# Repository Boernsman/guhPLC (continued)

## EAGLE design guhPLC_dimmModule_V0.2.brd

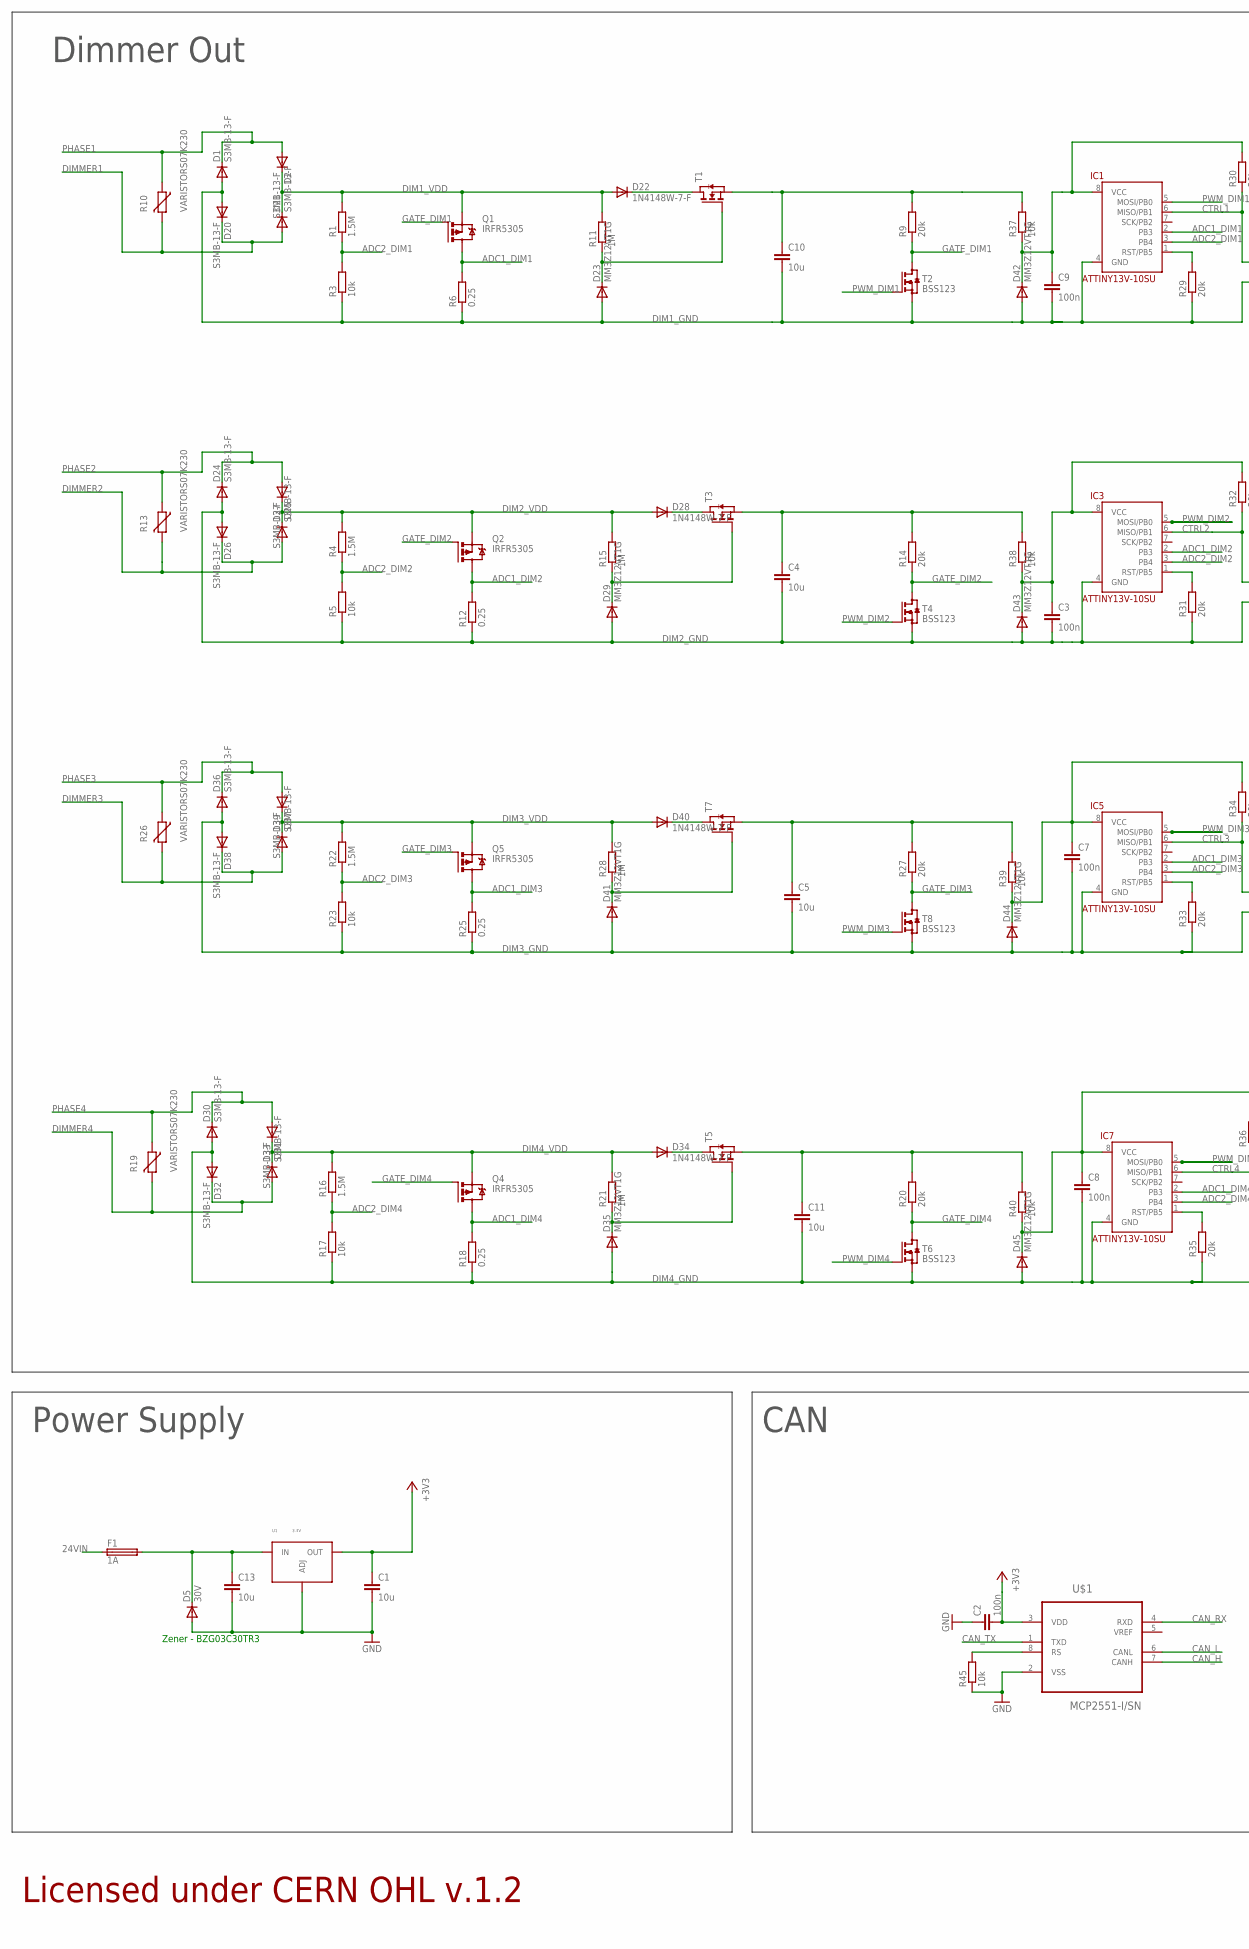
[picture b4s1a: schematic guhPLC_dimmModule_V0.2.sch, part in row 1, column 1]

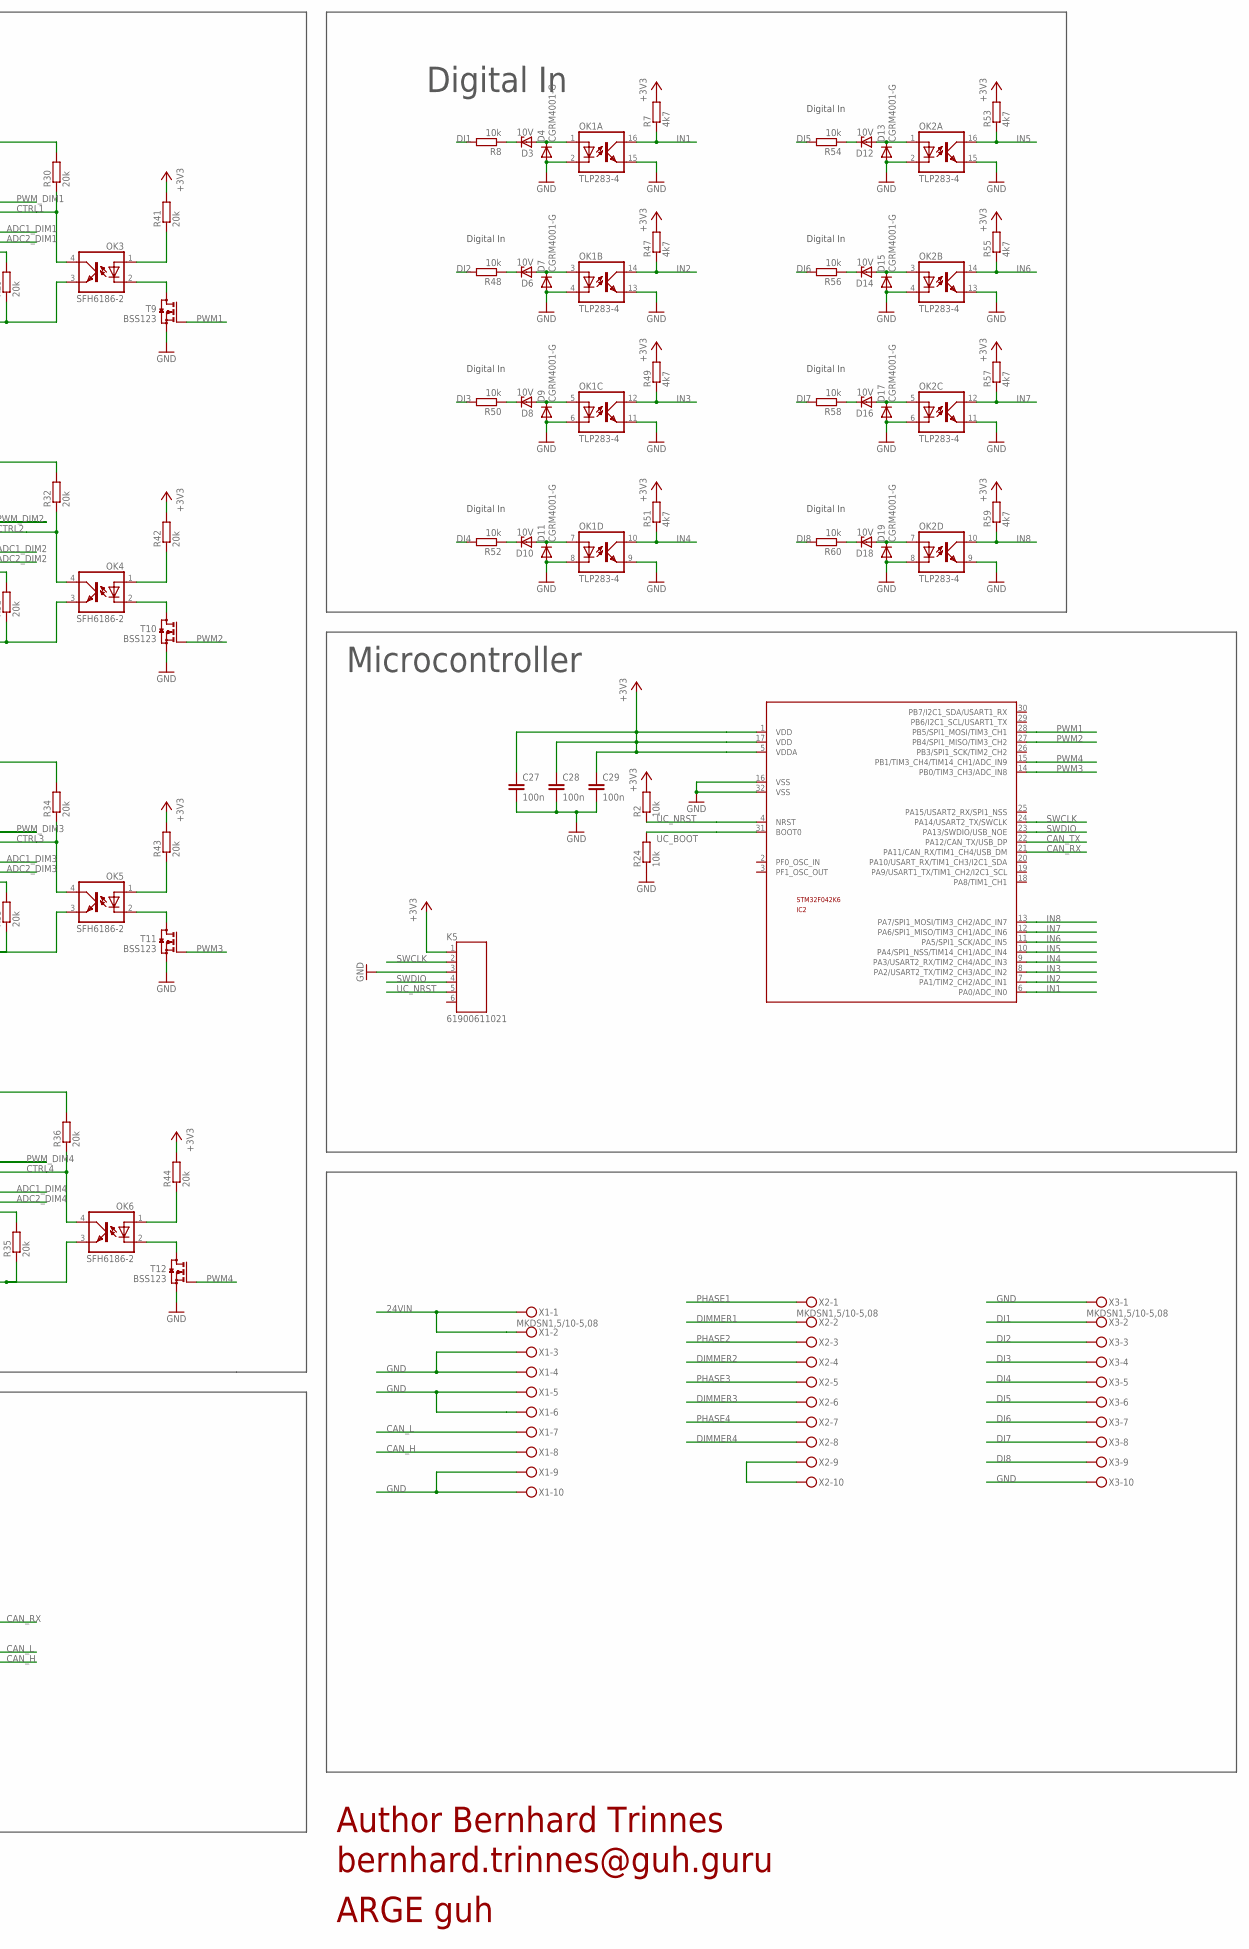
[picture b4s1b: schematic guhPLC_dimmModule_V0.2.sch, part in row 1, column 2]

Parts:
C1, C4, C5, C10, C11, C13: 10u; C1206
C2, C3, C7, C8, C9, C27, C28, C29: 100n; C0603
D1, D2, D20, D21, D24, D25, D26, D27, D30, D31, D32, D33, D36, D37, D38, D39: S3MB-13-F; DO214AA
D3, D6, D8, D10, D12, D14, D16, D18: 10V; SOD80C
D4, D7, D9, D11, D13, D15, D17, D19: CGRM4001-G; SOD-123_MINI-SMA
D5: 30V; DO214AC
D22, D28, D34, D40: 1N4148W-7-F; SOD123
D23, D29, D35, D41, D42, D43, D44, D45: MM3Z12VT1G; SOD323-W
F1: 1A; LITTLEFUSE
IC1, IC3, IC5, IC7: ATTINY13V-10SU; SOIC8
IC2: STM32F042K6; LQFP32-7X7
K5: 61900611021
OK1, OK2: TLP283-4; MINI-FLAT-16
OK3, OK4, OK5, OK6: SFH6186-2; SMD4
Q1, Q2, Q4, Q5: IRFR5305; D-PAK_TO252AA
R1: 1.5M; R1206
R2, R24, R45: 10k; R0603
R3: 10k; R1206
R4, R16, R22: 1.5M; M1206
R5, R17, R23, R37, R38, R39, R40: 10k; M1206
R6: 0.25; R1206
R7, R47, R49, R51, R53, R55, R57, R59: 4k7; R0603
R8, R48, R50, R52, R54, R56, R58, R60: 10k; R0805
R9, R14, R20, R27: 20k; M1206
R10, R13, R19, R26: VARISTORS07K230; S07K230
R11: 1M; R1206
R12, R18, R25: 0.25; M1206
R15, R21, R28: 1M; M1206
R29, R30, R31, R32, R33, R34, R35, R36, R41, R42, R43, R44: 20k; R0603
T1, T3, T5, T7: NMOSSOT23; SOT-23
T2, T4, T6, T8, T9, T10, T11, T12: BSS123; SOT23
U1: 3.3V; TO-252-3L
U$1: MCP2551-I/SN; SOIC127P600X175-8N
X1, X2, X3: MKDSN1,5/10-5,08

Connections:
24VIN: F1.1, X1.1, X1.2
+3V3: C1.1, C2.2, C27.1, C28.1, C29.1, IC2.1 (VDD), IC2.5 (VDDA), IC2.17 (VDD), K5.1, R2.2, R7.2, R41.2, R42.2, R43.2, R44.2, R47.2, R49.2, R51.2, R53.2, R55.2, R57.2, R59.2, U1.PAD (OUT), U$1.3 (VDD)
ADC1_DIM1: IC1.2 (PB3), Q1.4 (D), R6.2
ADC1_DIM2: IC3.2 (PB3), Q2.4 (D), R12.2
ADC1_DIM3: IC5.2 (PB3), Q5.4 (D), R25.2
ADC1_DIM4: IC7.2 (PB3), Q4.4 (D), R18.2
ADC2_DIM1: IC1.3 (PB4), R1.1, R3.2
ADC2_DIM2: IC3.3 (PB4), R4.1, R5.2
ADC2_DIM3: IC5.3 (PB4), R22.1, R23.2
ADC2_DIM4: IC7.3 (PB4), R16.1, R17.2
CAN_H: U$1.7 (CANH), X1.8
CAN_L: U$1.6 (CANL), X1.7
CAN_RX: IC2.21 (PA11/CAN_RX/TIM1_CH4/USB_DM), U$1.4 (RXD)
CAN_TX: IC2.22 (PA12/CAN_TX/USB_DP), U$1.1 (TXD)
CTRL1: IC1.6 (MISO/PB1), OK3.4 (COL), R30.1
CTRL2: IC3.6 (MISO/PB1), OK4.4 (COL), R32.1
CTRL3: IC5.6 (MISO/PB1), OK5.4 (COL), R34.1
CTRL4: IC7.6 (MISO/PB1), OK6.4 (COL), R36.1
DI1: R8.2, X3.2
DI2: R48.2, X3.3
DI3: R50.2, X3.4
DI4: R52.2, X3.5
DI5: R54.2, X3.6
DI6: R56.2, X3.7
DI7: R58.2, X3.8
DI8: R60.2, X3.9
DIM1_GND: C9.2, C10.2, D1.A, D20.A, D23.A, D42.A, IC1.4 (GND), OK3.3 (EMIT), R3.1, R6.1, R29.1, T2.2 (S)
DIM1_VDD: D2.C, D21.C, D22.A, Q1.3 (S), R1.2, R11.2
DIM2_GND: C3.2, C4.2, D24.A, D26.A, D29.A, D43.A, IC3.4 (GND), OK4.3 (EMIT), R5.1, R12.1, R31.1, T4.2 (S)
DIM2_VDD: D25.C, D27.C, D28.A, Q2.3 (S), R4.2, R15.2
DIM3_GND: C5.2, C7.2, D36.A, D38.A, D41.A, D44.A, IC5.4 (GND), OK5.3 (EMIT), R23.1, R25.1, R33.1, T8.2 (S)
DIM3_VDD: D37.C, D39.C, D40.A, Q5.3 (S), R22.2, R28.2
DIM4_GND: C8.2, C11.2, D30.A, D32.A, D35.A, D45.A, IC7.4 (GND), OK6.3 (EMIT), R17.1, R18.1, R35.1, T6.2 (S)
DIM4_VDD: D31.C, D33.C, D34.A, Q4.3 (S), R16.2, R21.2
DIMMER1: D20.C, D21.A, R10.2, X2.2
DIMMER2: D26.C, D27.A, R13.2, X2.4
DIMMER3: D38.C, D39.A, R26.2, X2.6
DIMMER4: D32.C, D33.A, R19.2, X2.8
GATE_DIM1: Q1.1 (G), R9.1, T2.3 (D)
GATE_DIM2: Q2.1 (G), R14.1, T4.3 (D)
GATE_DIM3: Q5.1 (G), R27.1, T8.3 (D)
GATE_DIM4: Q4.1 (G), R20.1, T6.3 (D)
GND: C1.2, C2.1, C13.2, C27.2, C28.2, C29.2, D4.A, D5.A, D7.A, D9.A, D11.A, D13.A, D15.A, D17.A, D19.A, IC2.16 (VSS), IC2.32 (VSS), K5.3, OK1.2 (C), OK1.4 (C), OK1.6 (C), OK1.8 (C), OK1.9 (EMIT), OK1.11 (EMIT), OK1.13 (EMIT), OK1.15 (EMIT), OK2.2 (C), OK2.4 (C), OK2.6 (C), OK2.8 (C), OK2.9 (EMIT), OK2.11 (EMIT), OK2.13 (EMIT), OK2.15 (EMIT), R24.1, R45.1, T9.2 (S), T10.2 (S), T11.2 (S), T12.2 (S), U1.1 (ADJ), U$1.2 (VSS), X1.3, X1.4, X1.5, X1.6, X1.9, X1.10, X3.1, X3.10
IN1: IC2.6 (PA0/ADC_IN0), OK1.16 (COL), R7.1
IN2: IC2.7 (PA1/TIM2_CH2/ADC_IN1), OK1.14 (COL), R47.1
IN3: IC2.8 (PA2/USART2_TX/TIM2_CH3/ADC_IN2), OK1.12 (COL), R49.1
IN4: IC2.9 (PA3/USART2_RX/TIM2_CH4/ADC_IN3), OK1.10 (COL), R51.1
IN5: IC2.10 (PA4/SPI1_NSS/TIM14_CH1/ADC_IN4), OK2.16 (COL), R53.1
IN6: IC2.11 (PA5/SPI1_SCK/ADC_IN5), OK2.14 (COL), R55.1
IN7: IC2.12 (PA6/SPI1_MISO/TIM3_CH1/ADC_IN6), OK2.12 (COL), R57.1
IN8: IC2.13 (PA7/SPI1_MOSI/TIM3_CH2/ADC_IN7), OK2.10 (COL), R59.1
unnamed: C8.1, D45.C, IC7.8 (VCC), R36.2, R40.1
unnamed: D29.C, R15.1, T3.3 (G)
unnamed: D28.C, T3.1 (D)
unnamed: D22.C, T1.1 (D)
unnamed: D23.C, R11.1, T1.3 (G)
unnamed: C9.1, D42.C, IC1.8 (VCC), R30.2, R37.1
unnamed: C3.1, D43.C, IC3.8 (VCC), R32.2, R38.1
unnamed: D3.C, R8.1
unnamed: D35.C, R21.1, T5.3 (G)
unnamed: D3.A, D4.C, OK1.1 (A)
unnamed: D34.C, T5.1 (D)
unnamed: C7.1, D44.C, IC5.8 (VCC), R34.2, R39.1
unnamed: D41.C, R28.1, T7.3 (G)
unnamed: D40.C, T7.1 (D)
unnamed: C10.1, R9.2, R37.2, T1.2 (S)
unnamed: OK3.1 (A), R41.1
unnamed: C4.1, R14.2, R38.2, T3.2 (S)
unnamed: OK3.2 (C), T9.3 (D)
unnamed: OK4.1 (A), R42.1
unnamed: C5.1, R27.2, R39.2, T7.2 (S)
unnamed: D6.C, R48.1
unnamed: OK4.2 (C), T10.3 (D)
unnamed: D6.A, D7.C, OK1.3 (A)
unnamed: OK5.1 (A), R43.1
unnamed: C11.1, R20.2, R40.2, T5.2 (S)
unnamed: IC5.1 (RST/PB5), R33.2
unnamed: OK5.2 (C), T11.3 (D)
unnamed: OK6.1 (A), R44.1
unnamed: OK6.2 (C), T12.3 (D)
unnamed: X2.9, X2.10
unnamed: R45.2, U$1.8 (RS)
unnamed: IC1.1 (RST/PB5), R29.2
unnamed: IC3.1 (RST/PB5), R31.2
unnamed: IC7.1 (RST/PB5), R35.2
unnamed: D8.C, R50.1
unnamed: D8.A, D9.C, OK1.5 (A)
unnamed: D10.C, R52.1
unnamed: D10.A, D11.C, OK1.7 (A)
unnamed: D12.C, R54.1
unnamed: D12.A, D13.C, OK2.1 (A)
unnamed: D14.C, R56.1
unnamed: D14.A, D15.C, OK2.3 (A)
unnamed: D16.C, R58.1
unnamed: D16.A, D17.C, OK2.5 (A)
unnamed: D18.C, R60.1
unnamed: D18.A, D19.C, OK2.7 (A)
PHASE1: D1.C, D2.A, R10.1, X2.1
PHASE2: D24.C, D25.A, R13.1, X2.3
PHASE3: D36.C, D37.A, R26.1, X2.5
PHASE4: D30.C, D31.A, R19.1, X2.7
PWM1: IC2.28 (PB5/SPI1_MOSI/TIM3_CH1), T9.1 (G)
PWM2: IC2.27 (PB4/SPI1_MISO/TIM3_CH2), T10.1 (G)
PWM3: IC2.14 (PB0/TIM3_CH3/ADC_IN8), T11.1 (G)
PWM4: IC2.15 (PB1/TIM3_CH4/TIM14_CH1/ADC_IN9), T12.1 (G)
PWM_DIM1: IC1.5 (MOSI/PB0), T2.1 (G)
PWM_DIM2: IC3.5 (MOSI/PB0), T4.1 (G)
PWM_DIM3: IC5.5 (MOSI/PB0), T8.1 (G)
PWM_DIM4: IC7.5 (MOSI/PB0), T6.1 (G)
SWCLK: IC2.24 (PA14/USART2_TX/SWCLK), K5.2
SWDIO: IC2.23 (PA13/SWDIO/USB_NOE), K5.4
UC_BOOT: IC2.31 (BOOT0), R24.2
UC_NRST: IC2.4 (NRST), K5.5, R2.1
VCC: C13.1, D5.C, F1.2, U1.2 (IN)

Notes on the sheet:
Microcontroller
Digital In
CAN
Zener - BZG03C30TR3
Power Supply
Dimmer Out
Author Bernhard Trinnes
ARGE guh
bernhard.trinnes@guh.guru
Licensed under CERN OHL v.1.2

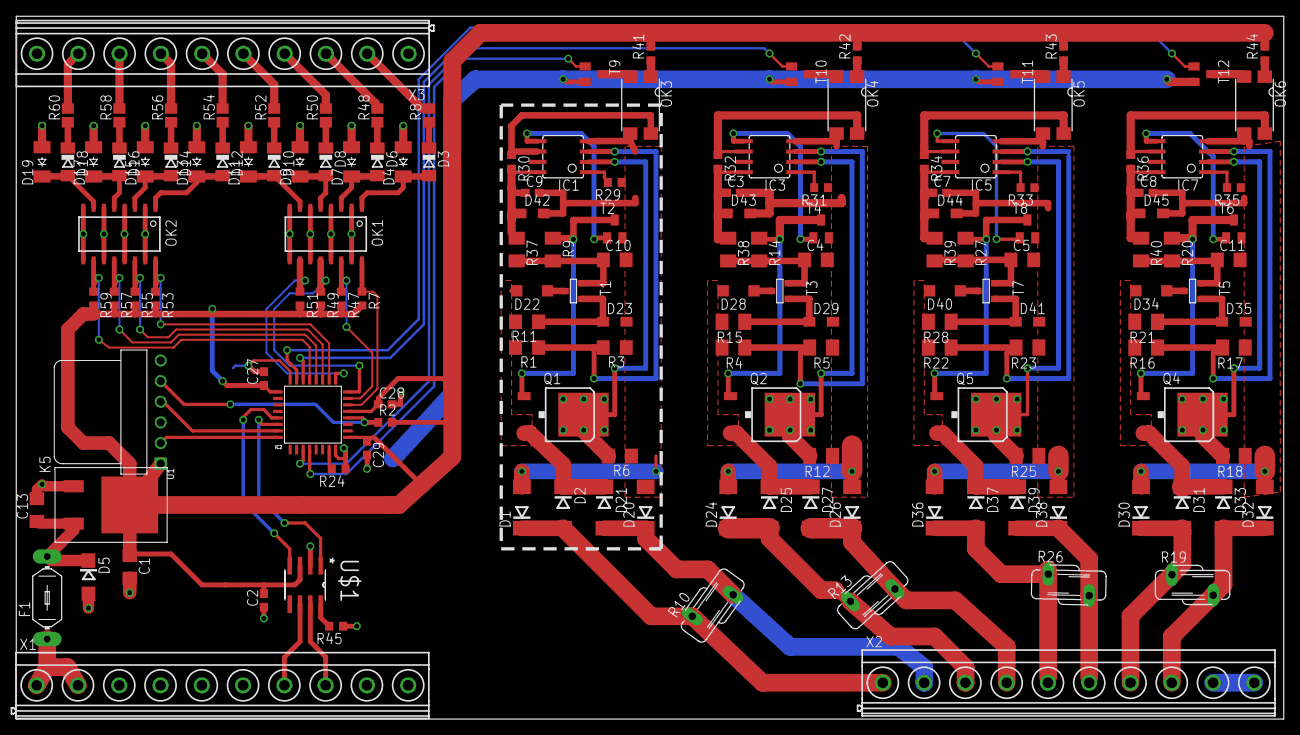
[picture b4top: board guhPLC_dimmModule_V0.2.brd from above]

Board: 2 copper layers, 156.0 x 86.5 mm, 152 parts (0 on the bottom side), 114 nets.

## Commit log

2015-08-14 initial project version
2015-08-16 added pull ups for i2C changed the port for the 32kHz crystal at STM32
2015-08-16 Readme.md updated
2015-08-16 Updated PDF
2015-08-18 Added license files
2015-08-18 Added License to README Minor bug fixes
2015-08-20 Added 1-wire interface
2015-08-20 Added guhPLC dimmer module initial version
2015-08-29 Dimmer module now with CAN instead of RS485 - uC changed to STM32F042K6
2015-08-31 Initial commit 6LowPan Module IEEE802.15.04 - 2.4GHz
2015-08-31 Changed RS485 to CAN Bus - for better multi master communication
2015-08-31 Removed old version of the dimmer module
2015-10-06 New Smart Meter Interface
